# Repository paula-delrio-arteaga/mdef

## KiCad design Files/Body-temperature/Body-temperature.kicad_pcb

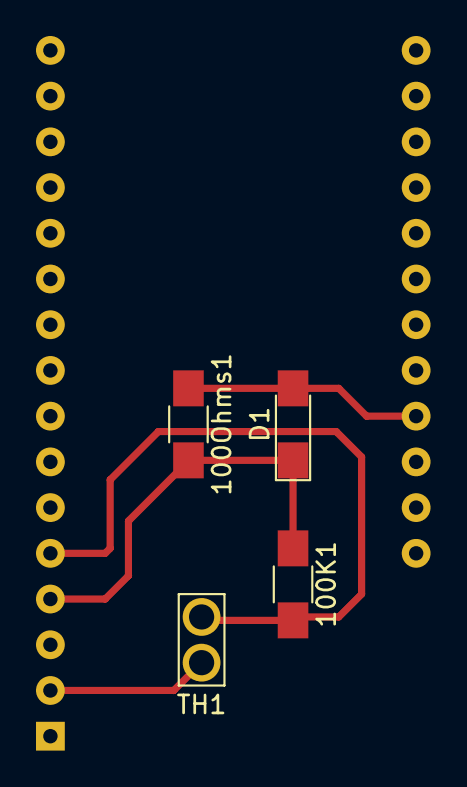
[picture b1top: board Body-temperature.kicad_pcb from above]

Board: 2 copper layers, 5 parts (1 on the bottom side), 4 nets.

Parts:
100K1, 100Ohms1: R; R_1206
A1: Adafruit_Feather_HUZZAH32_ESP32; Adafruit_Feather
D1: LED; LED_1206
TH1: Thermistor_NTC; PinHeader_1x02_P2.54mm_Vertical_THT_D1.4mm

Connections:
GND: 100K1.1, 100Ohms1.2, A1.4, D1.1
unnamed: 100K1.2, A1.5, TH1.2
PINA12: 100Ohms1.1, A1.25, D1.2
V3: A1.2, TH1.1

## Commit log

2021-10-10 my first commit
2021-10-11 website update
2021-10-11 update all
2021-10-11 /Users/pauladelrioarteaga/Documents/MDEF-2021/WEBSITE/assets/img
2021-10-13 commit on "master"
2021-10-13 main folder
2021-10-14 test
2021-10-19 update index
2021-10-19 update web
2021-10-19 update text
2021-10-30 update website
2021-11-03 update 3nov
2021-11-08 update LWYOI
2021-11-14 bio agri & design studio update
2021-11-19 bio and footer nav
2021-11-26 update tbtm
2021-12-11 update reflections
2021-12-23 mistakes spelling
2022-01-09 update corrections
2022-01-11 forensic report hackmd
2022-01-11 update a world in data hack dm report
2022-01-17 next billion secs
2022-02-02 new layout + fab academy
2022-02-07 remixing materialsand layout update
2022-02-08 design interventions 02
2022-02-11 weekly task 2 update plus design intervention
2022-02-17 update fab and design studio
2022-02-19 files
2022-02-20 Materials in context
2022-02-22 micro-challenge 1
2022-03-07 updates fabacademy
2022-03-07 week 6
2022-03-07 links fab academy
2022-03-07 orden columnas
2022-03-08 design studio update
2022-03-08 deleted repeated images
2022-03-08 video grasshopper fixed
2022-03-08 fabacademy landing links
2022-03-08 links update fab
2022-03-16 UPDATE FABACADEMY
2022-03-16 update files links git
2022-03-16 links to files - new tab
2022-03-16 links_button
2022-03-17 about link
2022-03-20 Atlas_weak_signals_02
2022-03-20 IMAGES
2022-05-18 fabacademy
2022-05-18 mold sensor file
2022-05-19 Fabacademy-update
2022-05-25 bioborg tab
2022-06-13 reflection
2022-06-13 note 17
2022-06-13 reflections
2022-06-16 More for Dafni
2022-06-17 CODE
